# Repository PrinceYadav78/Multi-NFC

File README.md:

# Smart NFC E-Ink Card

## What this is

this is a small custom pcb device i build which have a nfc antenna, e-ink display, flash storage and a microcontroller all together on one board. the idea is that the device can talk with phone using nfc and also show some info on the e-ink screen. the screen is very low power so it can keep the image even when power is not used.

the board also have a small battery and charging circuit so it can run portable. the main chip used here is the nrf52840 which handle the nfc and other logic of the board. there is also external flash memory to store some data and firmware stuff.

## Why i build this

i mostly build this project to learn how full hardware design works from start to end. like making schematic, pcb layout, antenna design and power system. before this i never made a board with nfc and battery and display together so i wanted to try it.

also i thought it would be cool to have something like a programmable nfc card which can change what it shows on the display. it could be used for things like smart tags, id cards, small info display or just experimenting with embedded hardware.

so the main goal was learning and building something fun at same time :)

## Hardware Visualization

### Full Schematic

### PCB Layout

### 3D Render

### BOM

## Bill of Materials (BOM)

| PCB                                                                                                       |                                                                                 |     |               |                        |               |            |
|-----------------------------------------------------------------------------------------------------------|---------------------------------------------------------------------------------|-----|---------------|------------------------|---------------|------------|
| Part                                                                                                      | Link                                                                            | Qty | Cost per Unit | Footprint              | JLCPCB Part # | Total Cost |
| Material                                                                                                  | https://jlcpcb.com/                                                             | 1   | 3.42          |                        |               | 3.42       |
| Body Outline Tolerance                                                                                    | https://jlcpcb.com/                                                             | 1   | 8.42          |                        |               | 8.42       |
| 4-Wire Kelvin Test                                                                                        | https://jlcpcb.com/                                                             | 1   | 16.73         |                        |               | 16.73      |
| Min via Hole size/diameter                                                                                | https://jlcpcb.com/                                                             | 1   | 34.22         |                        |               | 34.22      |
| PCB                                                                                                       | https://jlcpcb.com/                                                             | 1   | 7             |                        |               | 7          |
|                                                                                                           |                                                                                 |     |               | TOTAL                  |               | 69.79      |
|                                                                                                           |                                                                                 |     |               |                        |               |            |
| PCBA                                                                                                      |                                                                                 |     |               |                        |               |            |
| Part                                                                                                      | Link                                                                            | Qty | Cost per Unit | Footprint              | JLCPCB Part # | Total Cost |
| Setup Fee                                                                                                 | https://jlcpcb.com/                                                             | 1   | 50.74         |                        |               | 50.74      |
| Stencil                                                                                                   | https://jlcpcb.com/                                                             | 1   | 16.3          |                        |               | 16.3       |
| Hand Soldering Labor Fee                                                                                  | https://jlcpcb.com/                                                             | 1   | 3.55          |                        |               | 3.55       |
| Manual Assembly                                                                                           | https://jlcpcb.com/                                                             | 1   | 0.65          |                        |               | 0.65       |
| PCB Assembly Fixture                                                                                      | https://jlcpcb.com/                                                             | 1   | 16.3          |                        |               | 16.3       |
| Packing Fee                                                                                               | https://jlcpcb.com/                                                             | 1   | 0.49          |                        |               | 0.49       |
| Feeders Loading Fee                                                                                       | https://jlcpcb.com/                                                             | 1   | 27.36         |                        |               | 27.36      |
| SMT Assembly                                                                                              | https://jlcpcb.com/                                                             | 1   | 1.07          |                        |               | 1.07       |
|                                                                                                           |                                                                                 |     |               | TOTAL                  |               | 116.46     |
|                                                                                                           |                                                                                 |     |               |                        |               |            |
| Components                                                                                                |                                                                                 |     |               |                        |               |            |
| Part                                                                                                      | Link                                                                            | Qty | Cost per Unit | Footprint              | JLCPCB Part # | Total Cost |
| ABM11W-32.0000MHZ-8-B1U-T3                                                                                | https://jlcpcb.com/partdetail/2077318-ABM11W_32_0000MHZ_8_B1UT3/C1985774        | 2   | 0.86          | ABM11W300000MHZ4B1UT3  | C1985774      | 1.7234     |
| SKRPACE010                                                                                                | https://jlcpcb.com/partdetail/ALPSALPINE-SKRPACE010/C139797                     | 6   | 0.07          | SMT_4.2X3.2_           | C139797       | 0.4032     |
| USB4085-GF-A_REVA4                                                                                        | https://jlcpcb.com/partdetail/8061907-USB4085_GFA/C7095263                      | 2   | 1.39          | GCT_USB4085-GF-A_REVA4 | C7095263      | 2.786      |
| 150pF                                                                                                     | https://jlcpcb.com/partdetail/1879-0402B151K500NT/C1527                         | 20  | 0.0012        | 402                    | C1527         | 0.024      |
| 10uF                                                                                                      | https://jlcpcb.com/partdetail/16204-CL05A106MQ5NUNC/C15525                      | 20  | 0.0055        | 402                    | C15525        | 0.11       |
| ABS06-32.768KHZ-9-T                                                                                       | https://jlcpcb.com/partdetail/AbraconLLC-ABS06_32_768KHZ_9T/C1985410            | 2   | 1.9242        | ABS06                  | C1985410      | 3.8484     |
| 12pF                                                                                                      | https://jlcpcb.com/partdetail/1899-0402CG120J500NT/C1547                        | 20  | 0.0011        | 402                    | C1547         | 0.022      |
| 1uF                                                                                                       | https://jlcpcb.com/partdetail/53938-CL05A105KA5NQNC/C52923                      | 20  | 0.0041        | 402                    | C52923        | 0.082      |
| 1k                                                                                                        | https://jlcpcb.com/partdetail/12256-0402WGF1001TCE/C11702                       | 20  | 0.0007        | 402                    | C11702        | 0.014      |
| MCP73831T-2ATI_OT                                                                                         | https://jlcpcb.com/partdetail/MicrochipTech-MCP73831T_2ATIOT/C14879             | 2   | 0.9961        | SOT95P270X145-5N       | C14879        | 1.9922     |
| 5.1k                                                                                                      | https://jlcpcb.com/partdetail/26648-0402WGF5101TCE/C25905                       | 40  | 0.0008        | 402                    | C25905        | 0.016      |
| nRF52840-QFAA-F-R7                                                                                        | https://jlcpcb.com/partdetail/NordicSemicon-NRF52840_QFAA_FR7/C3606653          | 2   | 5.1481        | QFN40P600X600X95-49N-D | C3606653      | 10.2962    |
| 0.1uF                                                                                                     | https://jlcpcb.com/partdetail/1877-CL05B104KO5NNNC/C1525                        | 30  | 0.0013        | 402                    | C1525         | 0.039      |
| W25Q16JVUXIQ_TR                                                                                           | https://jlcpcb.com/partdetail/WinbondElec-W25Q16JVUXIQ/C2843335                 | 2   | 1.3977        | SON50P300X200X60-9N    | C2843335      | 2.7954     |
| LED                                                                                                       | https://jlcpcb.com/partdetail/Hubei_KENTOElec-KT0603R/C2286                     | 20  | 0.0064        | 603                    | C2286         | 0.128      |
| 10k                                                                                                       | https://jlcpcb.com/partdetail/26487-0402WGF1002TCE/C25744                       | 20  | 0.0008        | 402                    | C25744        | 0.016      |
| TPS78833DBVR                                                                                              | https://jlcpcb.com/partdetail/TexasInstruments-TPS78833DBVR/C2869019            | 2   | 1.706         | SOT95P280X145-5N       | C2869019      | 3.412      |
| 2k                                                                                                        | https://jlcpcb.com/partdetail/4516-0402WGF2001TCE/C4109                         | 20  | 0.0008        | 402                    | C4109         | 0.016      |
| 4.7uF                                                                                                     | https://jlcpcb.com/partdetail/24469-CL05A475MP5NRNC/C23733                      | 20  | 0.005         | 402                    | C23733        | 0.1        |
| Waveshare 2.9 inch e-Ink Paper Display Module with SPI Interface                                          | https://robu.in/product/2-9-inch-e-ink-paper-display-module-with-spi-interface/ | 2   | 17.325        |                        |               | 34.65      |
| WLY551145 3.7V 250mAh 1S LiPo Battery – Micro Rechargeable Battery Pack for Wearables / Micro Drone / IoT | https://robu.in/product/250mah-pcm-protected-micro-li-po-battery/               | 2   | 2.222         |                        |               | 4.444      |
|                                                                                                           |                                                                                 |     |               | TOTAL                  |               | 66.9178    |
|                                                                                                           |                                                                                 |     |               |                        |               |            |
| Shipping                                                                                                  |                                                                                 |     |               |                        |               |            |
| Part                                                                                                      | Link                                                                            | Qty | Cost per Unit | Footprint              | JLCPCB Part # | Total Cost |
| Shipping                                                                                                  | https://jlcpcb.com                                                              | 1   | 14.21         |                        |               | 14.21      |
|                                                                                                           |                                                                                 |     |               | TOTAL                  |               | 14.21      |
|                                                                                                           |                                                                                 |     |               |                        |               |            |
| 3D-Printing                                                                                               |                                                                                 |     |               |                        |               |            |
| Part                                                                                                      | Link                                                                            | Qty | Cost per Unit | Footprint              | JLCPCB Part # | Total Cost |
| 3D-Printing                                                                                               | https://jlc3dp.com/                                                             | 2   | 9.45          |                        |               | 18.9       |
|                                                                                                           |                                                                                 |     |               | TOTAL                  |               | 18.9       |

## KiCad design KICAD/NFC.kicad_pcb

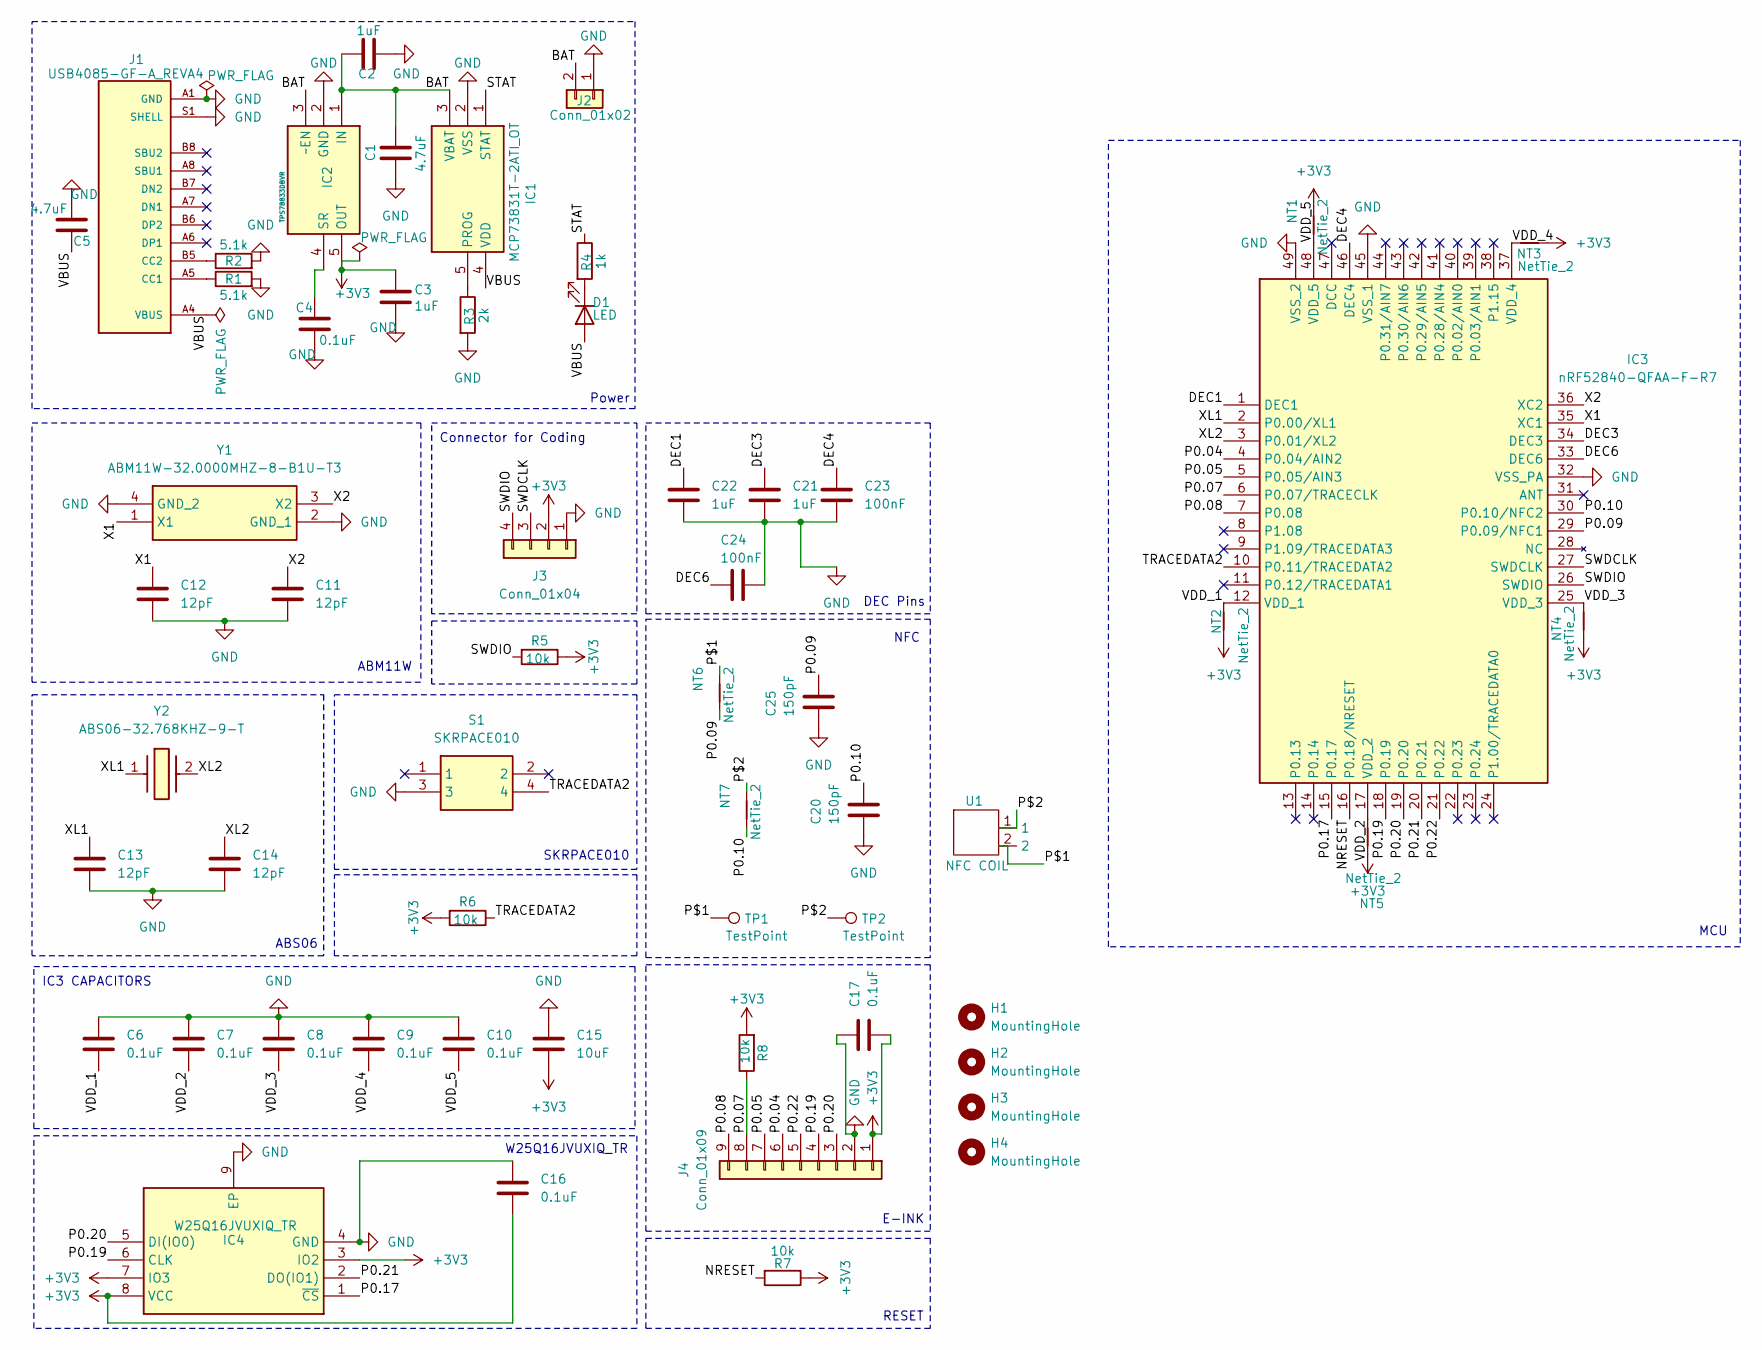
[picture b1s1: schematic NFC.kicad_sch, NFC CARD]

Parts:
C1, C5: 4.7uF; C_0402_1005Metric_Pad0.74x0.62mm_HandSolder
C2, C3, C21, C22: 1uF; C_0402_1005Metric_Pad0.74x0.62mm_HandSolder
C4, C6, C7, C8, C9, C10, C16, C17: 0.1uF; C_0402_1005Metric_Pad0.74x0.62mm_HandSolder
C11, C12, C13, C14: 12pF; C_0402_1005Metric_Pad0.74x0.62mm_HandSolder
C15: 10uF; C_0402_1005Metric_Pad0.74x0.62mm_HandSolder
C20, C25: 150pF; C_0402_1005Metric_Pad0.74x0.62mm_HandSolder
C23, C24: 100nF; C_0402_1005Metric_Pad0.74x0.62mm_HandSolder
D1: LED; LED_0603_1608Metric_Pad1.05x0.95mm_HandSolder
H1, H2, H3, H4: MountingHole; MountingHole_2.5mm
IC1: MCP73831T-2ATI_OT; SOT95P270X145-5N; Manufacturer_Part_Number MCP73831T-2ATI/OT; Mouser Part Number 579-MCP73831T-2ATIOT
IC2: TPS78833DBVR; SOT95P280X145-5N; Manufacturer_Part_Number TPS78833DBVR; Mouser Part Number 595-TPS78833DBVR
IC3: nRF52840-QFAA-F-R7; QFN40P600X600X95-49N-D; Manufacturer_Part_Number nRF52840-QFAA-F-R7; Mouser Part Number 949-NRF52840QFAAF-R7
IC4: W25Q16JVUXIQ_TR; SON50P300X200X60-9N; Manufacturer_Part_Number W25Q16JVUXIQ TR; Mouser Part Number 454-W25Q16JVUXIQTR
J1: USB4085-GF-A_REVA4; GCT_USB4085-GF-A_REVA4; PARTREV A4
J2: Conn_01x02; PinHeader_1x02_P1.27mm_Vertical
J3: Conn_01x04; PinHeader_1x04_P1.27mm_Vertical
J4: Conn_01x09; PinHeader_1x09_P1.27mm_Vertical
NT1, NT2, NT3, NT4, NT5, NT6, NT7: NetTie_2; NetTie-2_SMD_Pad0.5mm
R1, R2: 5.1k; R_0402_1005Metric_Pad0.72x0.64mm_HandSolder
R3: 2k; R_0402_1005Metric_Pad0.72x0.64mm_HandSolder
R4: 1k; R_0402_1005Metric_Pad0.72x0.64mm_HandSolder
R5, R6, R7, R8: 10k; R_0402_1005Metric_Pad0.72x0.64mm_HandSolder
S1: SKRPACE010; SMT_4.2X3.2_; Manufacturer_Part_Number SKRPACE010; Mouser Part Number 688-SKRPACE010
TP1, TP2: TestPoint; TestPoint_Pad_D1.0mm
U1: NFC COIL; Untitled
Y1: ABM11W-32.0000MHZ-8-B1U-T3; ABM11W300000MHZ4B1UT3; Manufacturer_Part_Number ABM11W-32.0000MHZ-8-B1U-T3; Mouser Part Number 815-11W32-8B1UT
Y2: ABS06-32.768KHZ-9-T; ABS06; Manufacturer_Part_Number ABS06-32.768KHZ-9-T; Mouser Part Number 815-ABS06-32.7KHZ9-T

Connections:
+3V3: C3.1, C15.2, C16.2, C17.2, IC2.5 (OUT), IC4.3 (IO2), IC4.7 (IO3), IC4.8 (VCC), J3.2, J4.1, NT1.1, NT2.2, NT3.1, NT4.2, NT5.2, R5.1, R6.2, R7.1, R8.2
/BAT: C1.1, C2.1, IC1.3 (VBAT), IC2.1 (IN), IC2.3 (~EN), J2.2
/DEC1: C22.1, IC3.1 (DEC1)
/DEC3: C21.1, IC3.34 (DEC3)
/DEC4: C23.1, IC3.46 (DEC4)
/DEC6: C24.1, IC3.33 (DEC6)
/NRESET: IC3.16 (P0.18/NRESET), R7.2
/P0.04: IC3.4 (P0.04/AIN2), J4.6
/P0.05: IC3.5 (P0.05/AIN3), J4.7
/P0.07: IC3.6 (P0.07/TRACECLK), J4.8, R8.1
/P0.08: IC3.7 (P0.08), J4.9
/P0.09: C25.2, IC3.29 (P0.09/NFC1), NT6.2
/P0.10: C20.2, IC3.30 (P0.10/NFC2), NT7.2
/P0.17: IC3.15 (P0.17), IC4.1 (~CS)
/P0.19: IC3.18 (P0.19), IC4.6 (CLK), J4.4
/P0.20: IC3.19 (P0.20), IC4.5 (DI(IO0)), J4.3
/P0.21: IC3.20 (P0.21), IC4.2 (DO(IO1))
/P0.22: IC3.21 (P0.22), J4.5
/P$1: NT6.1, TP1.1, U1.2; also elsewhere on the board
/P$2: NT7.1, TP2.1, U1.1; also elsewhere on the board
/STAT: IC1.1 (STAT), R4.1
/SWDCLK: IC3.27 (SWDCLK), J3.3
/SWDIO: IC3.26 (SWDIO), J3.4, R5.2
/TRACEDATA2: IC3.10 (P0.11/TRACEDATA2), R6.1, S1.4
/VDD_1: C6.2, IC3.12 (VDD_1), NT2.1
/VDD_2: C7.2, IC3.17 (VDD_2), NT5.1
/VDD_3: C8.2, IC3.25 (VDD_3), NT4.1
/VDD_4: C9.2, IC3.37 (VDD_4), NT3.2
/VDD_5: C10.2, IC3.48 (VDD_5), NT1.2
/X1: C12.1, IC3.35 (XC1), Y1.1 (X1)
/X2: C11.1, IC3.36 (XC2), Y1.3 (X2)
/XL1: C13.1, IC3.2 (P0.00/XL1), Y2.1
/XL2: C14.1, IC3.3 (P0.01/XL2), Y2.2
GND: C1.2, C2.2, C3.2, C4.2, C5.2, C6.1, C7.1, C8.1, C9.1, C10.1, C11.2, C12.2, C13.2, C14.2, C15.1, C16.1, C17.1, C20.1, C21.2, C22.2, C23.2, C24.2, C25.1, IC1.2 (VSS), IC2.2 (GND), IC3.32 (VSS_PA), IC3.45 (VSS_1), IC3.49 (VSS_2), IC4.4 (GND), IC4.9 (EP), J1.A1 (GND), J1.A12 (GND), J1.B1 (GND), J1.B12 (GND), J1.S1 (SHELL), J1.S2 (SHELL), J1.S3 (SHELL), J1.S4 (SHELL), J2.1, J3.1, J4.2, R1.2, R2.2, R3.2, S1.3, Y1.2 (GND_1), Y1.4 (GND_2)
unnamed: D1.1 (K), R4.2
unnamed: IC1.5 (PROG), R3.1
unnamed: C4.1, IC2.4 (SR)
unnamed: J1.A5 (CC1), R1.1
unnamed: J1.B5 (CC2), R2.1
VBUS: C5.1, D1.2 (A), IC1.4 (VDD), J1.A4 (VBUS), J1.A9 (VBUS), J1.B4 (VBUS), J1.B9 (VBUS)

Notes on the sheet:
E-INK
Power
IC3 CAPACITORS
Connector for Coding
NFC
DEC Pins
RESET
MCU
W25Q16JVUXIQ_TR
SKRPACE010
ABS06
ABM11W

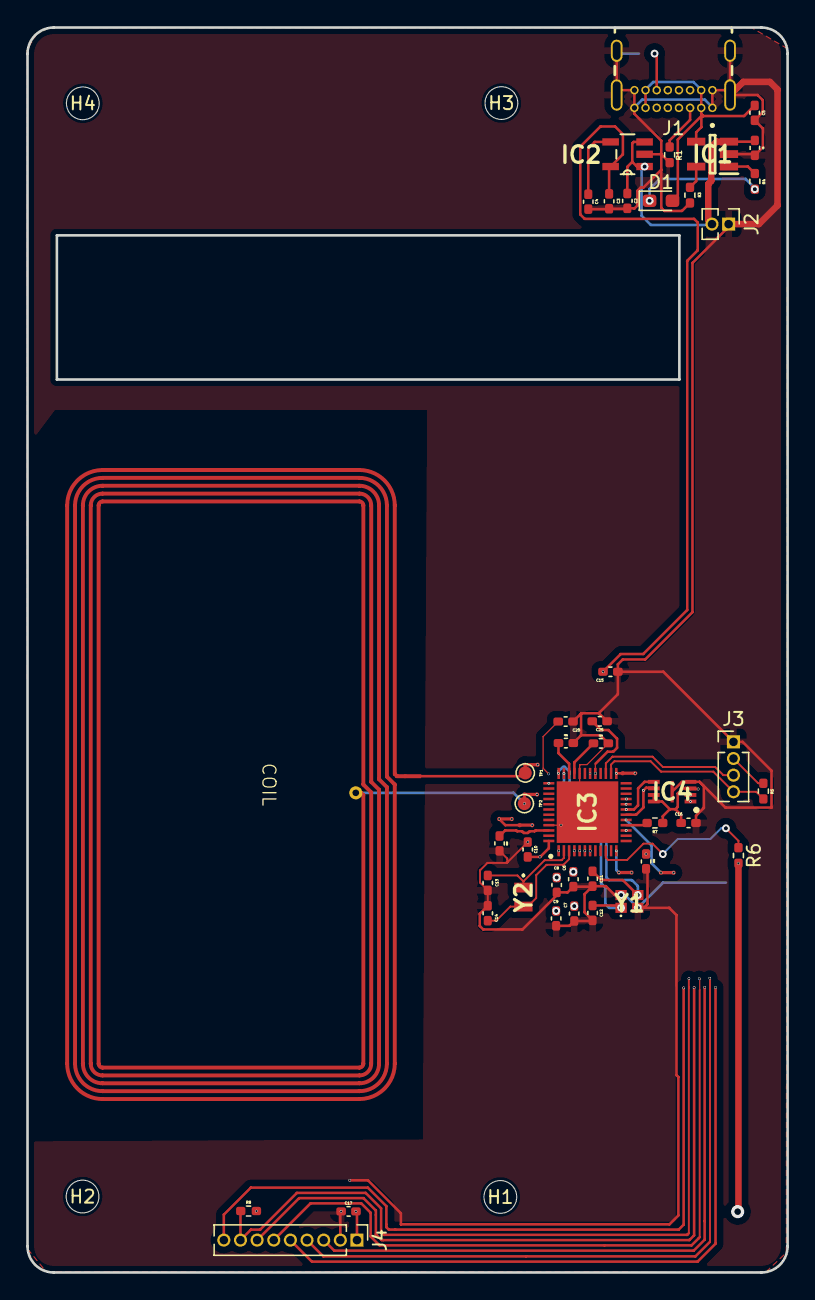
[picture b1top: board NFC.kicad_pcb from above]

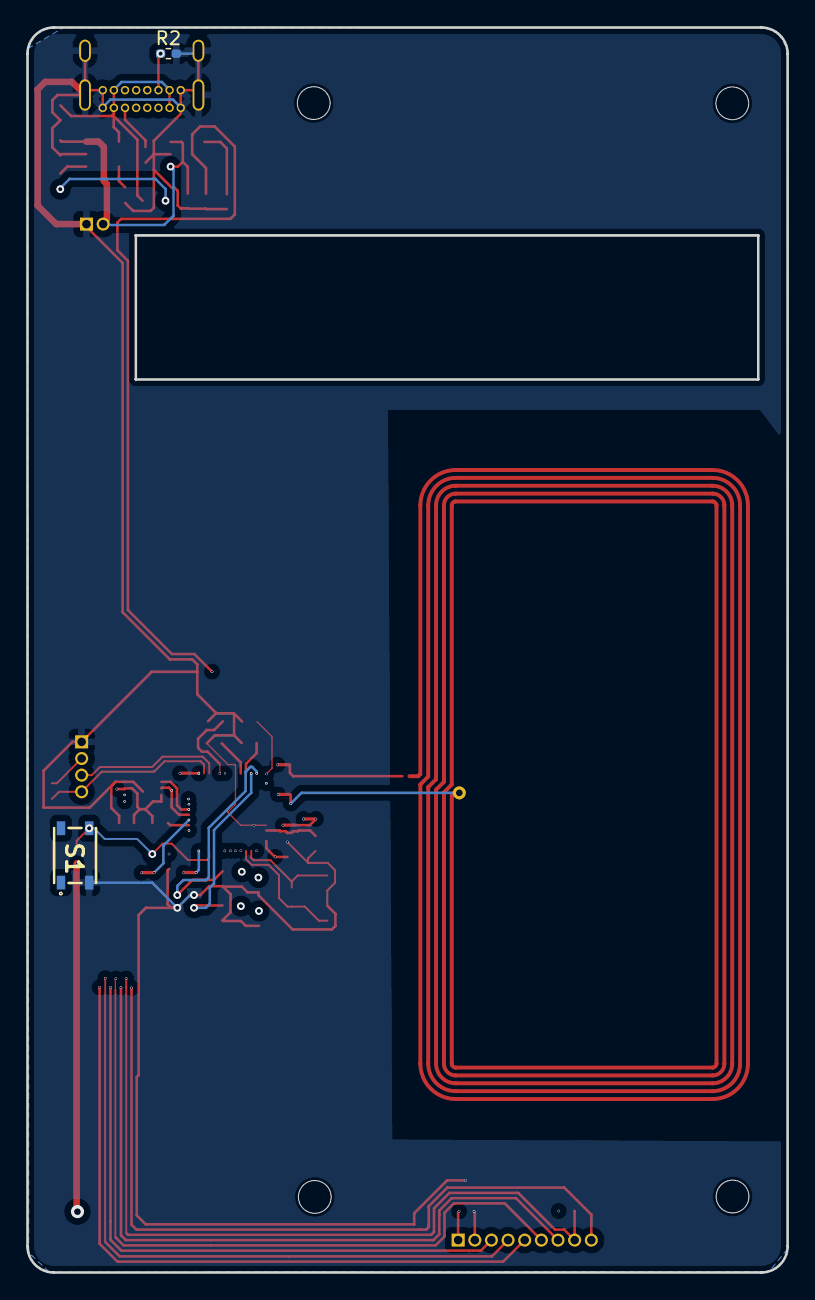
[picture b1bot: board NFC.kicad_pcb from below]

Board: 4 copper layers, 58.0 x 95.0 mm, 57 parts (2 on the bottom side), 40 nets.

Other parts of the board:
COIL: NFC; Untitled

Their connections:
/P$1: COIL.2; also elsewhere on the board
/P$2: COIL.1; also elsewhere on the board

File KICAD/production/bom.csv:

Designator,Footprint,Quantity,Value,LCSC Part #
"C1, C5",0402,2,4.7uF,
"C10, C16, C17, C4, C6, C7, C8, C9",0402,8,0.1uF,
"C11, C12, C13, C14",0402,4,12pF,
C15,0402,1,10uF,
"C2, C21, C22, C3",0402,4,1uF,
"C20, C25",0402,2,150pF,
"C23, C24",0402,2,100nF,
COIL,Untitled,1,NFC,
D1,0603,1,LED,
IC1,SOT95P270X145-5N,1,MCP73831T-2ATI_OT,
IC2,SOT95P280X145-5N,1,TPS78833DBVR,
IC3,QFN40P600X600X95-49N-D,1,nRF52840-QFAA-F-R7,
IC4,SON50P300X200X60-9N,1,W25Q16JVUXIQ_TR,
J1,GCT_USB4085-GF-A_REVA4,1,USB4085-GF-A_REVA4,
J2,PinHeader_1x02_P1.27mm_Vertical,1,Conn_01x02,
J3,PinHeader_1x04_P1.27mm_Vertical,1,Conn_01x04,
J4,PinHeader_1x09_P1.27mm_Vertical,1,Conn_01x09,
"R1, R2",0402,2,5.1k,
R3,0402,1,2k,
R4,0402,1,1k,
"R5, R6, R7, R8",0402,4,10k,
S1,SMT_4.2X3.2_,1,SKRPACE010,
"TP1, TP2",TestPoint_Pad_D1.0mm,2,TestPoint,
Y1,ABM11W300000MHZ4B1UT3,1,ABM11W-32.0000MHZ-8-B1U-T3,
Y2,ABS06,1,ABS06-32.768KHZ-9-T,

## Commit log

2026-03-09 firmware push
2026-03-09 step
2026-03-09 Fixed merge conflicts in firmware files
